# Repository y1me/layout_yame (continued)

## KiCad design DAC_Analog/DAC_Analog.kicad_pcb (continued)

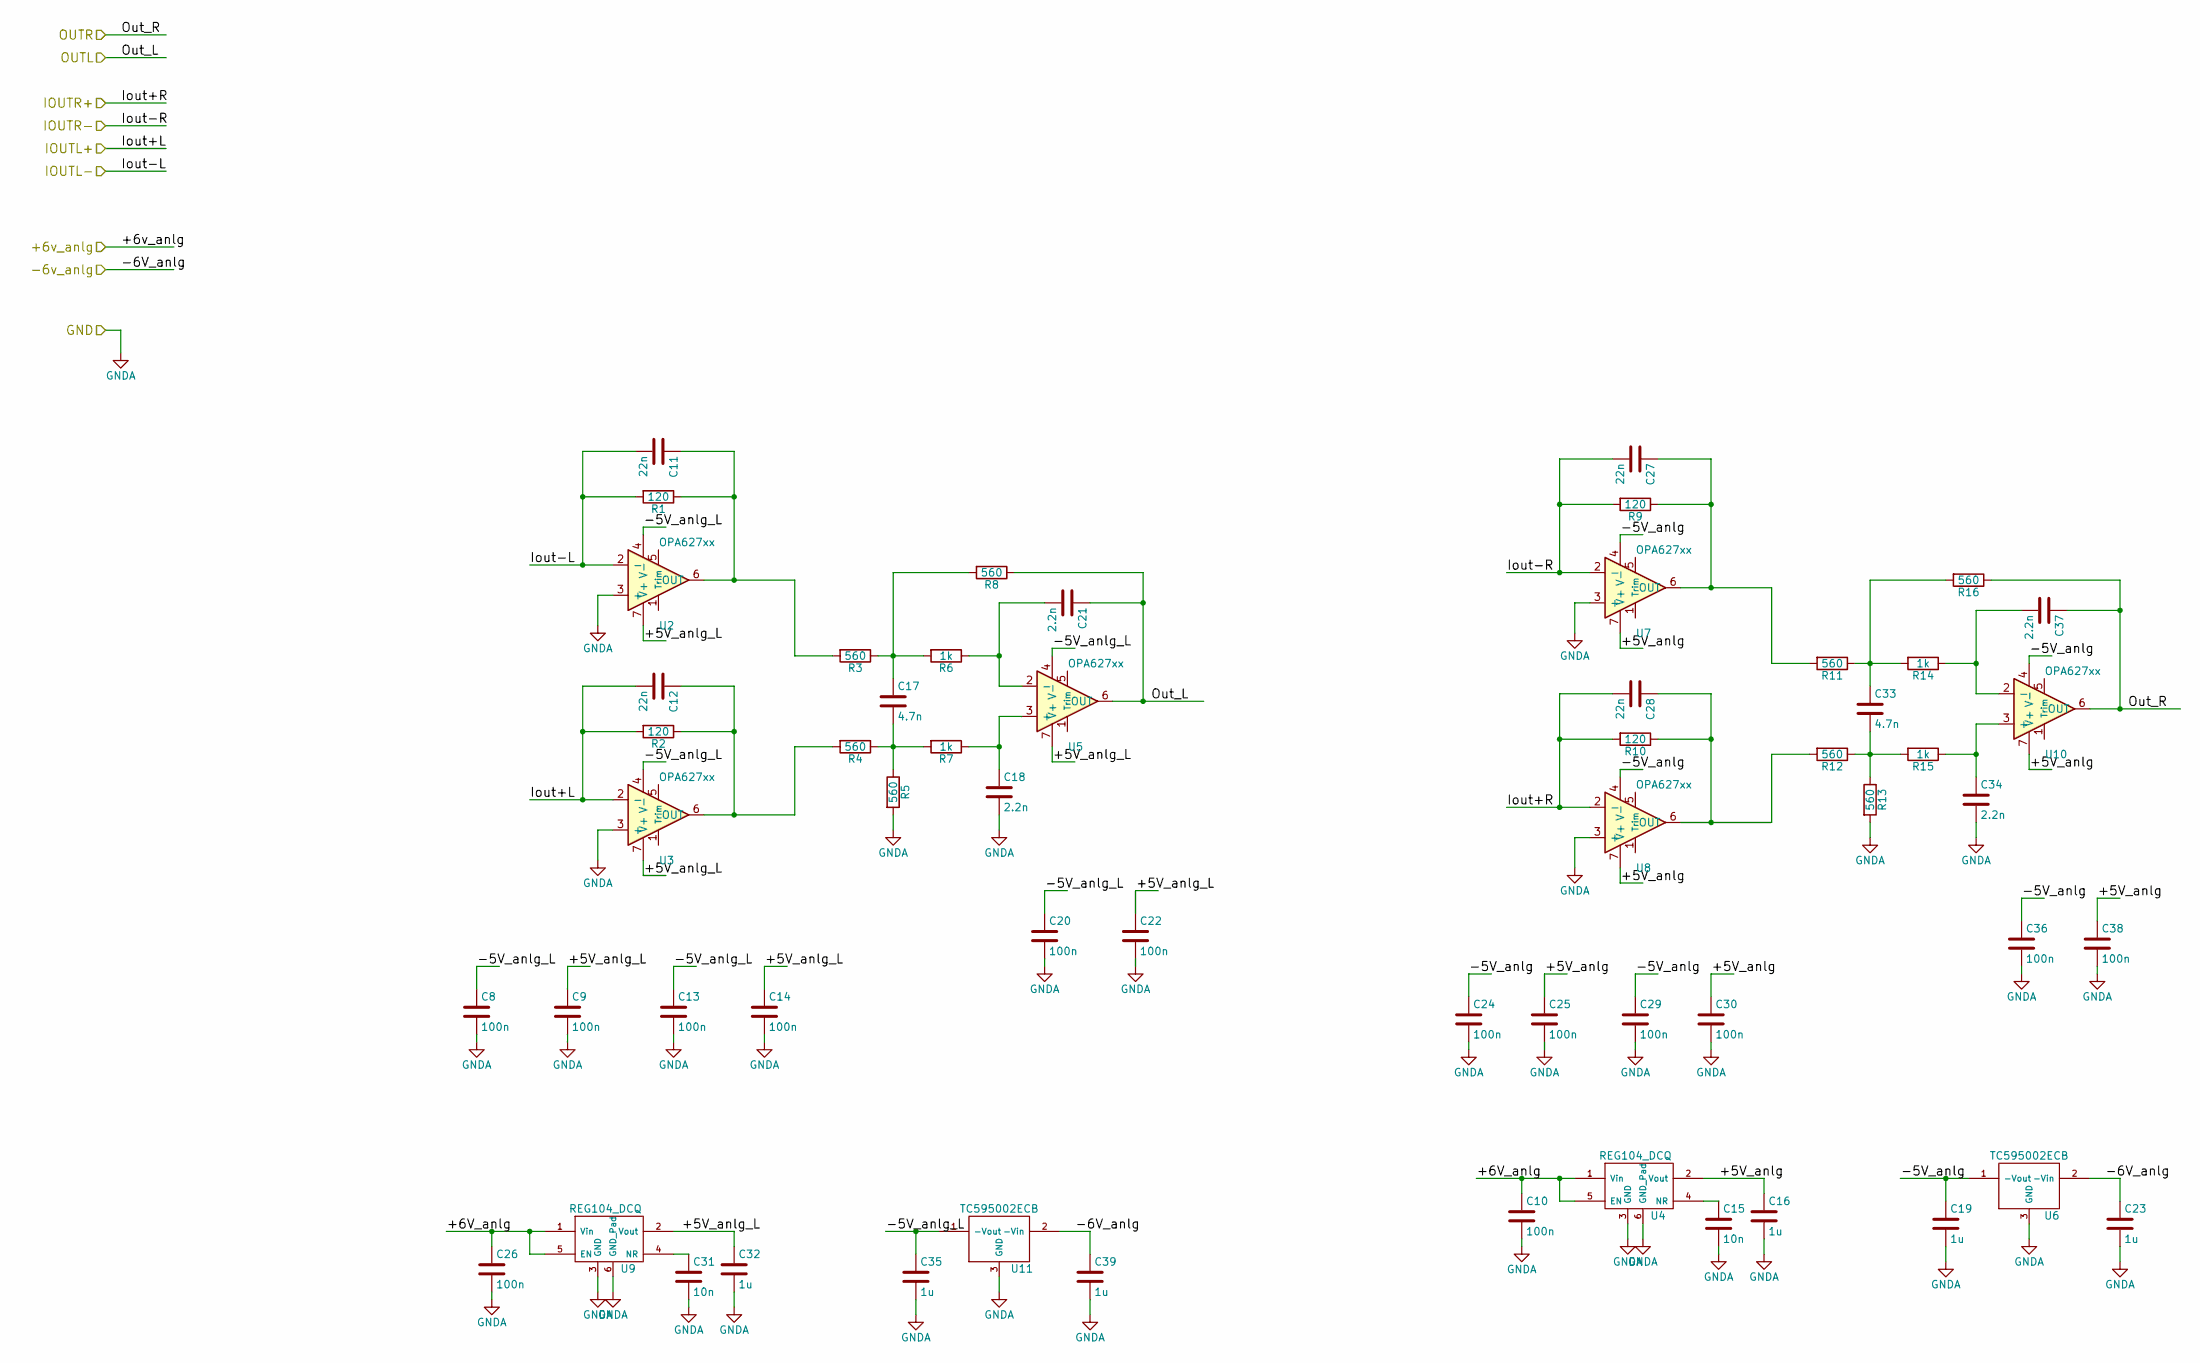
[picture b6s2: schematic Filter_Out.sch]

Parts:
C8, C9, C10, C13, C14, C20, C22, C24, C25, C26, C29, C30, C36, C38: 100n; SM0603-MR
C11, C12, C27, C28: 22n; C_Rect_L10.3mm_W5.0mm_P7.50mm_MKS4
C15, C31: 10n; SM0603-MR
C16, C19, C23, C32, C35, C39: 1u; SM0805-MR
C17, C33: 4.7n; C_Disc_D11.0mm_W5.0mm_P5.00mm
C18, C21, C34, C37: 2.2n; C_Disc_D11.0mm_W5.0mm_P5.00mm
R1, R2, R9, R10: 120; SM0603-MR
R3, R4, R5, R8, R11, R12, R13, R16: 560; SM0603-MR
R6, R7, R14, R15: 1k; SM0603-MR
U2, U3, U5, U7, U8, U10: OPA627xx; DIP-8_W7.62mm_Socket_LongPads
U4, U9: REG104_DCQ; SOT-223-6
U6, U11: TC595002ECB; SOT23-MR

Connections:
/+6v_anlg: C10.1, C26.1, U4.1 (Vin), U4.5 (EN), U9.1 (Vin), U9.5 (EN); also elsewhere on the board
/-6V_anlg: C23.1, C39.1, U6.2 (-Vin), U11.2 (-Vin); also elsewhere on the board
/Filter_Out/+5V_anlg: C16.1, C25.1, C30.1, C38.1, U4.2 (Vout), U7.7 (V+), U8.7 (V+), U10.7 (V+)
/Filter_Out/+5V_anlg_L: C9.1, C14.1, C22.1, C32.1, U2.7 (V+), U3.7 (V+), U5.7 (V+), U9.2 (Vout)
/Filter_Out/-5V_anlg: C19.1, C24.1, C29.1, C36.1, U6.1 (-Vout), U7.4 (V-), U8.4 (V-), U10.4 (V-)
/Filter_Out/-5V_anlg_L: C8.1, C13.1, C20.1, C35.1, U2.4 (V-), U3.4 (V-), U5.4 (V-), U11.1 (-Vout)
/IOUTL_N: C11.2, R1.2, U2.2 (-); also elsewhere on the board
/IOUTL_P: C12.2, R2.2, U3.2 (-); also elsewhere on the board
/IOUTR_N: C27.2, R9.2, U7.2 (-); also elsewhere on the board
/IOUTR_P: C28.2, R10.2, U8.2 (-); also elsewhere on the board
/Out_L: C21.1, R8.1, U5.6 (OUT); also elsewhere on the board
/Out_R: C37.1, R16.1, U10.6 (OUT); also elsewhere on the board
GND: C8.2, C9.2, C10.2, C13.2, C14.2, C15.2, C16.2, C18.2, C19.2, C20.2, C22.2, C23.2, C24.2, C25.2, C26.2, C29.2, C30.2, C31.2, C32.2, C34.2, C35.2, C36.2, C38.2, C39.2, R5.2, R13.2, U2.3 (+), U3.3 (+), U4.3 (GND), U4.6 (GND_Pad), U6.3 (GND), U7.3 (+), U8.3 (+), U9.3 (GND), U9.6 (GND_Pad), U11.3 (GND); also elsewhere on the board
unnamed: C11.1, R1.1, R3.2, U2.6 (OUT)
unnamed: C12.1, R2.1, R4.2, U3.6 (OUT)
unnamed: C15.1, U4.4 (NR)
unnamed: C17.1, R3.1, R6.2, R8.2
unnamed: C17.2, R4.1, R5.1, R7.2
unnamed: C18.1, R7.1, U5.3 (+)
unnamed: C21.2, R6.1, U5.2 (-)
unnamed: C27.1, R9.1, R11.2, U7.6 (OUT)
unnamed: C28.1, R10.1, R12.2, U8.6 (OUT)
unnamed: C31.1, U9.4 (NR)
unnamed: C33.1, R11.1, R14.2, R16.2
unnamed: C33.2, R12.1, R13.1, R15.2
unnamed: C34.1, R15.1, U10.3 (+)
unnamed: C37.2, R14.1, U10.2 (-)

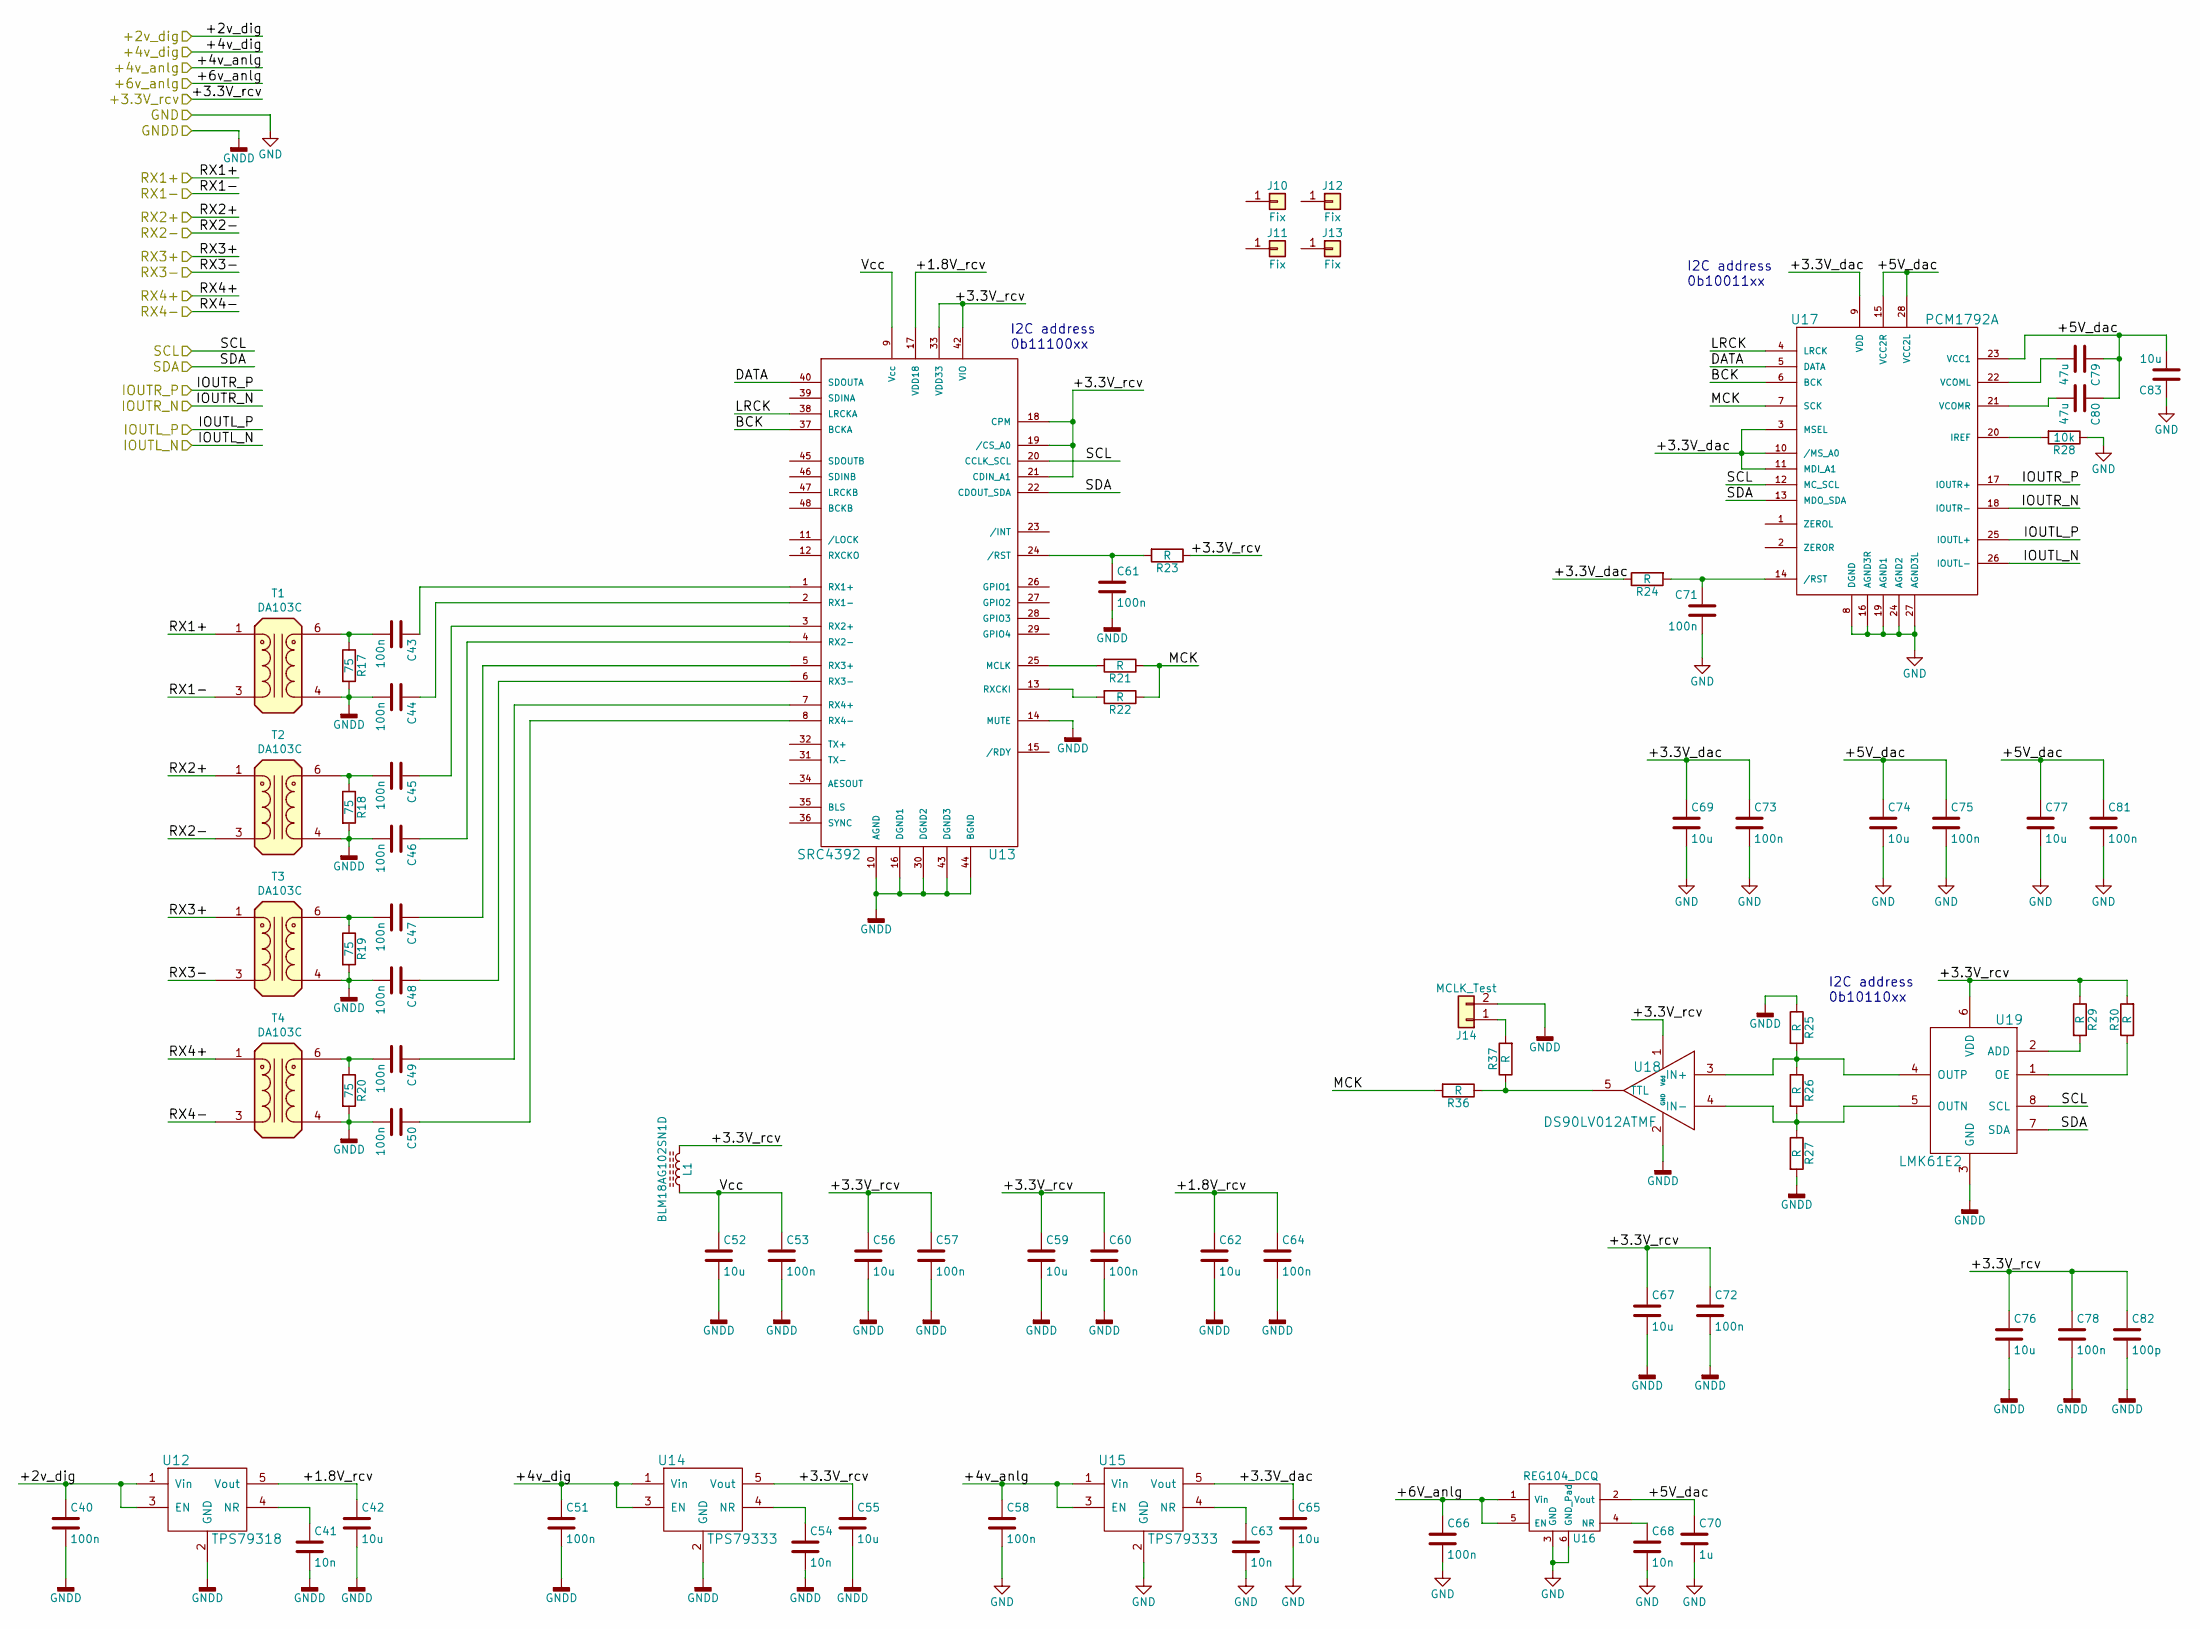
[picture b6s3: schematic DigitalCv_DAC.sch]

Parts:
C40, C43, C44, C45, C46, C47, C48, C49, C50, C51, C53, C57, C58, C60, C61, C64, C66, C71, C72, C73, C75, C78, C81: 100n; SM0603-MR
C41, C54, C63, C68: 10n; SM0603-MR
C42, C52, C55, C56, C59, C62, C65, C67, C69, C74, C76, C77, C83: 10u; SM0805-MR
C70: 1u; SM0805-MR
C79, C80: 47u; SM1206-MR
C82: 100p; SM0603-MR
J10, J11, J12, J13: Fix; MountingHole_3.2mm_M3
J14: MCLK_Test; Pin_Header_Straight_1x02_Pitch2.54mm
L1: BLM18AG102SN1D; SM0603-MR
R17, R18, R19, R20: 75; SM0603-MR
R21, R22, R23, R24, R25, R26, R27, R29, R30, R36, R37: R; SM0603-MR
R28: 10k; SM0603-MR
T1, T2, T3, T4: DA103C; DIP-6_W10.16mm_LongPads
U12: TPS79318; SOT-23-5_HandSoldering
U13: SRC4392; TQFP-48_7x7mm_Pitch0.5mm
U14, U15: TPS79333; SOT-23-5_HandSoldering
U16: REG104_DCQ; SOT-223-6
U17: PCM1792A; SSOP-28_5.3x10.2mm_Pitch0.65mm
U18: DS90LV012ATMF; SOT-23-5_HandSoldering
U19: LMK61E2; QFM_8

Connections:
/+2v_dig: C40.1, U12.1 (Vin), U12.3 (EN); also elsewhere on the board
/+3.3V_rcv: C55.1, C56.1, C57.1, C59.1, C60.1, C67.1, C72.1, C76.1, C78.1, C82.1, L1.1, R23.1, R29.1, R30.2, U13.18 (CPM), U13.19 (/CS_A0), U13.21 (CDIN_A1), U13.33 (VDD33), U13.42 (VIO), U14.5 (Vout), U18.1 (Vdd), U19.6 (VDD); also elsewhere on the board
/+4v_anlg: C58.1, U15.1 (Vin), U15.3 (EN); also elsewhere on the board
/+4v_dig: C51.1, U14.1 (Vin), U14.3 (EN); also elsewhere on the board
/+6v_anlg: C66.1, U16.1 (Vin), U16.5 (EN); also elsewhere on the board
/DigitalCv_DAC/+1.8V_rcv: C42.1, C62.1, C64.1, U12.5 (Vout), U13.17 (VDD18)
/DigitalCv_DAC/+3.3V_dac: C65.1, C69.1, C73.1, R24.1, U15.5 (Vout), U17.3 (MSEL), U17.9 (VDD), U17.10 (/MS_A0), U17.11 (MDI_A1)
/DigitalCv_DAC/+5V_dac: C70.1, C74.1, C75.1, C77.1, C79.1, C80.1, C81.1, C83.2, U16.2 (Vout), U17.15 (VCC2R), U17.23 (VCC1), U17.28 (VCC2L)
/DigitalCv_DAC/BCK: U13.37 (BCKA), U17.6 (BCK)
/DigitalCv_DAC/DATA: U13.40 (SDOUTA), U17.5 (DATA)
/DigitalCv_DAC/LRCK: U13.38 (LRCKA), U17.4 (LRCK)
/DigitalCv_DAC/MCK: R21.1, R22.1, R36.2, U17.7 (SCK)
/DigitalCv_DAC/Vcc: C52.1, C53.1, L1.2, U13.9 (Vcc)
/IOUTL_N: U17.26 (IOUTL-); also elsewhere on the board
/IOUTL_P: U17.25 (IOUTL+); also elsewhere on the board
/IOUTR_N: U17.18 (IOUTR-); also elsewhere on the board
/IOUTR_P: U17.17 (IOUTR+); also elsewhere on the board
/RX1+: T1.1 (AA); also elsewhere on the board
/RX1-: T1.3 (AB); also elsewhere on the board
/RX2+: T2.1 (AA); also elsewhere on the board
/RX2-: T2.3 (AB); also elsewhere on the board
/RX3+: T3.1 (AA); also elsewhere on the board
/RX3-: T3.3 (AB); also elsewhere on the board
/RX4+: T4.1 (AA); also elsewhere on the board
/RX4-: T4.3 (AB); also elsewhere on the board
/SCL: U13.20 (CCLK_SCL), U17.12 (MC_SCL), U19.8 (SCL); also elsewhere on the board
/SDA: U13.22 (CDOUT_SDA), U17.13 (MDO_SDA), U19.7 (SDA); also elsewhere on the board
GND: C40.2, C41.2, C42.2, C44.2, C46.2, C48.2, C50.2, C51.2, C52.2, C53.2, C54.2, C55.2, C56.2, C57.2, C58.2, C59.2, C60.2, C61.2, C62.2, C63.2, C64.2, C65.2, C66.2, C67.2, C68.2, C69.2, C70.2, C71.2, C72.2, C73.2, C74.2, C75.2, C76.2, C77.2, C78.2, C81.2, C82.2, C83.1, J14.2, R17.2, R18.2, R19.2, R20.2, R25.1, R27.2, R28.1, T1.4 (SA), T2.4 (SA), T3.4 (SA), T4.4 (SA), U12.2 (GND), U13.10 (AGND), U13.14 (MUTE), U13.16 (DGND1), U13.30 (DGND2), U13.43 (DGND3), U13.44 (BGND), U14.2 (GND), U15.2 (GND), U16.3 (GND), U16.6 (GND_Pad), U17.8 (DGND), U17.16 (AGND3R), U17.19 (AGND1), U17.24 (AGND2), U17.27 (AGND3L), U18.2 (GND), U19.3 (GND); also elsewhere on the board
unnamed: C41.1, U12.4 (NR)
unnamed: C43.1, U13.1 (RX1+)
unnamed: C43.2, R17.1, T1.6 (SB)
unnamed: C44.1, U13.2 (RX1-)
unnamed: C45.1, U13.3 (RX2+)
unnamed: C45.2, R18.1, T2.6 (SB)
unnamed: C46.1, U13.4 (RX2-)
unnamed: C47.1, U13.5 (RX3+)
unnamed: C47.2, R19.1, T3.6 (SB)
unnamed: C48.1, U13.6 (RX3-)
unnamed: C49.1, U13.7 (RX4+)
unnamed: C49.2, R20.1, T4.6 (SB)
unnamed: C50.1, U13.8 (RX4-)
unnamed: C54.1, U14.4 (NR)
unnamed: C61.1, R23.2, U13.24 (/RST)
unnamed: C63.1, U15.4 (NR)
unnamed: C68.1, U16.4 (NR)
unnamed: C71.1, R24.2, U17.14 (/RST)
unnamed: C79.2, U17.22 (VCOML)
unnamed: C80.2, U17.21 (VCOMR)
unnamed: J14.1, R37.2
unnamed: R21.2, U13.25 (MCLK)
unnamed: R22.2, U13.13 (RXCKI)
unnamed: R25.2, R26.1, U18.3 (IN+), U19.4 (OUTP)
unnamed: R26.2, R27.1, U18.4 (IN-), U19.5 (OUTN)
unnamed: R28.2, U17.20 (IREF)
unnamed: R29.2, U19.2 (ADD)
unnamed: R30.1, U19.1 (OE)
unnamed: R36.1, R37.1, U18.5 (TTL)

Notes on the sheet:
I2C address 0b11100xx
I2C address 0b10011xx
I2C address 0b10110xx

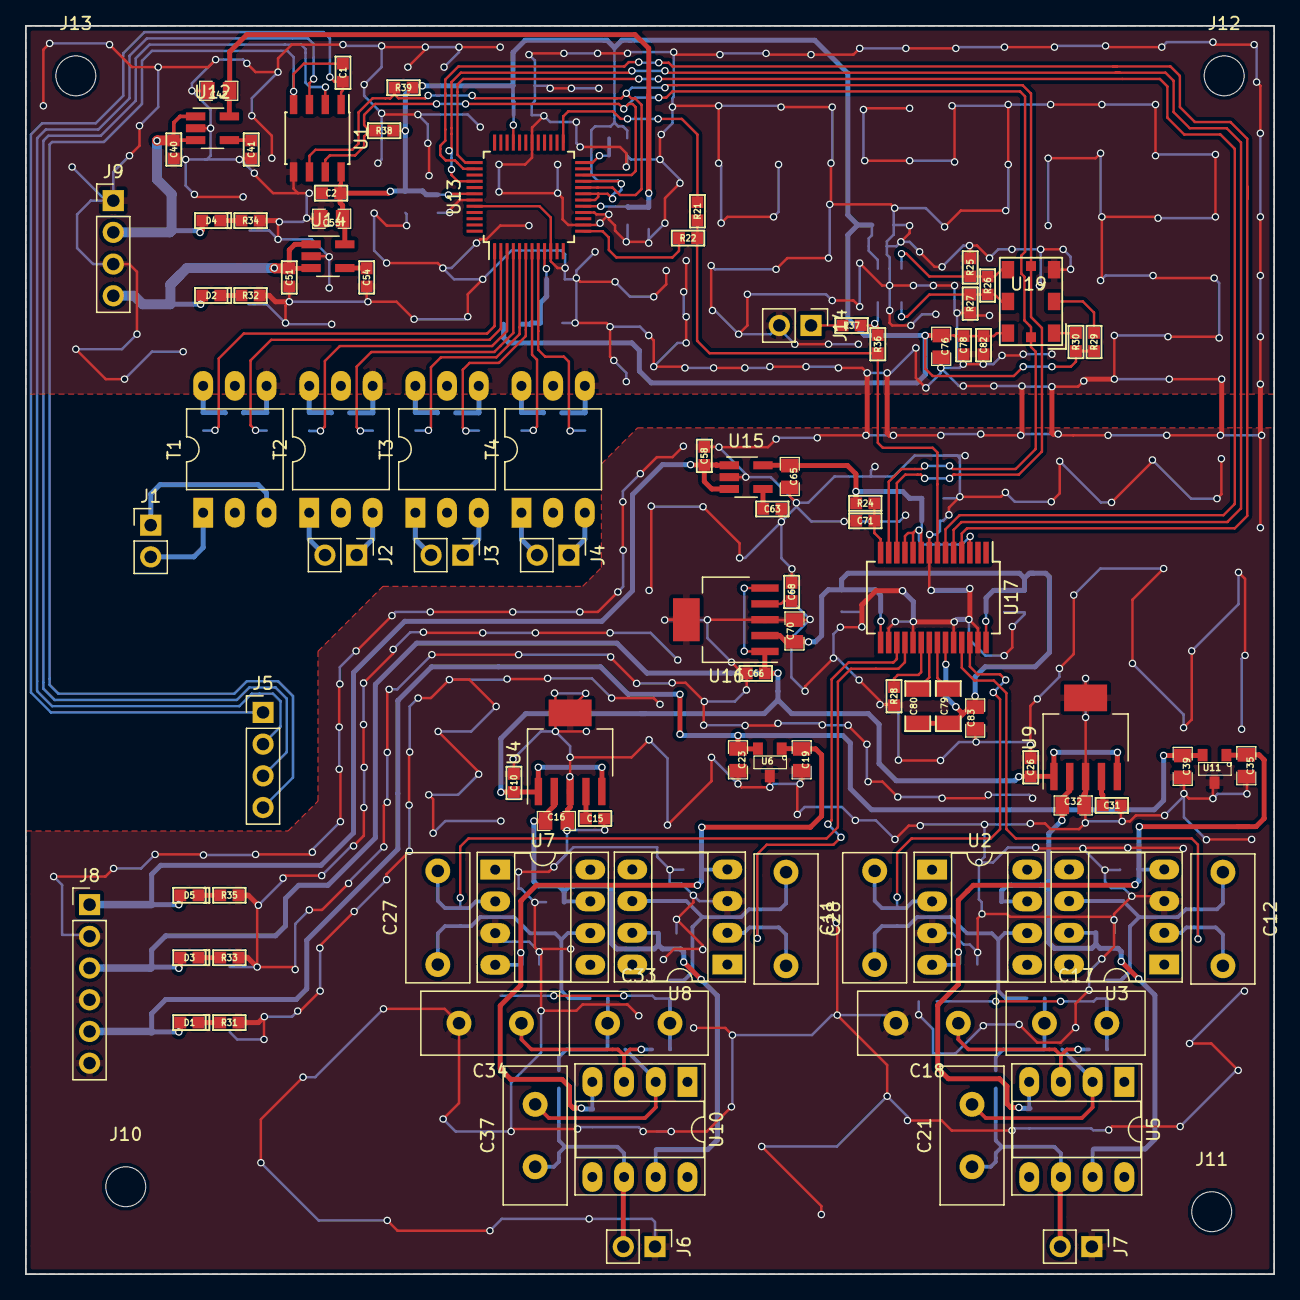
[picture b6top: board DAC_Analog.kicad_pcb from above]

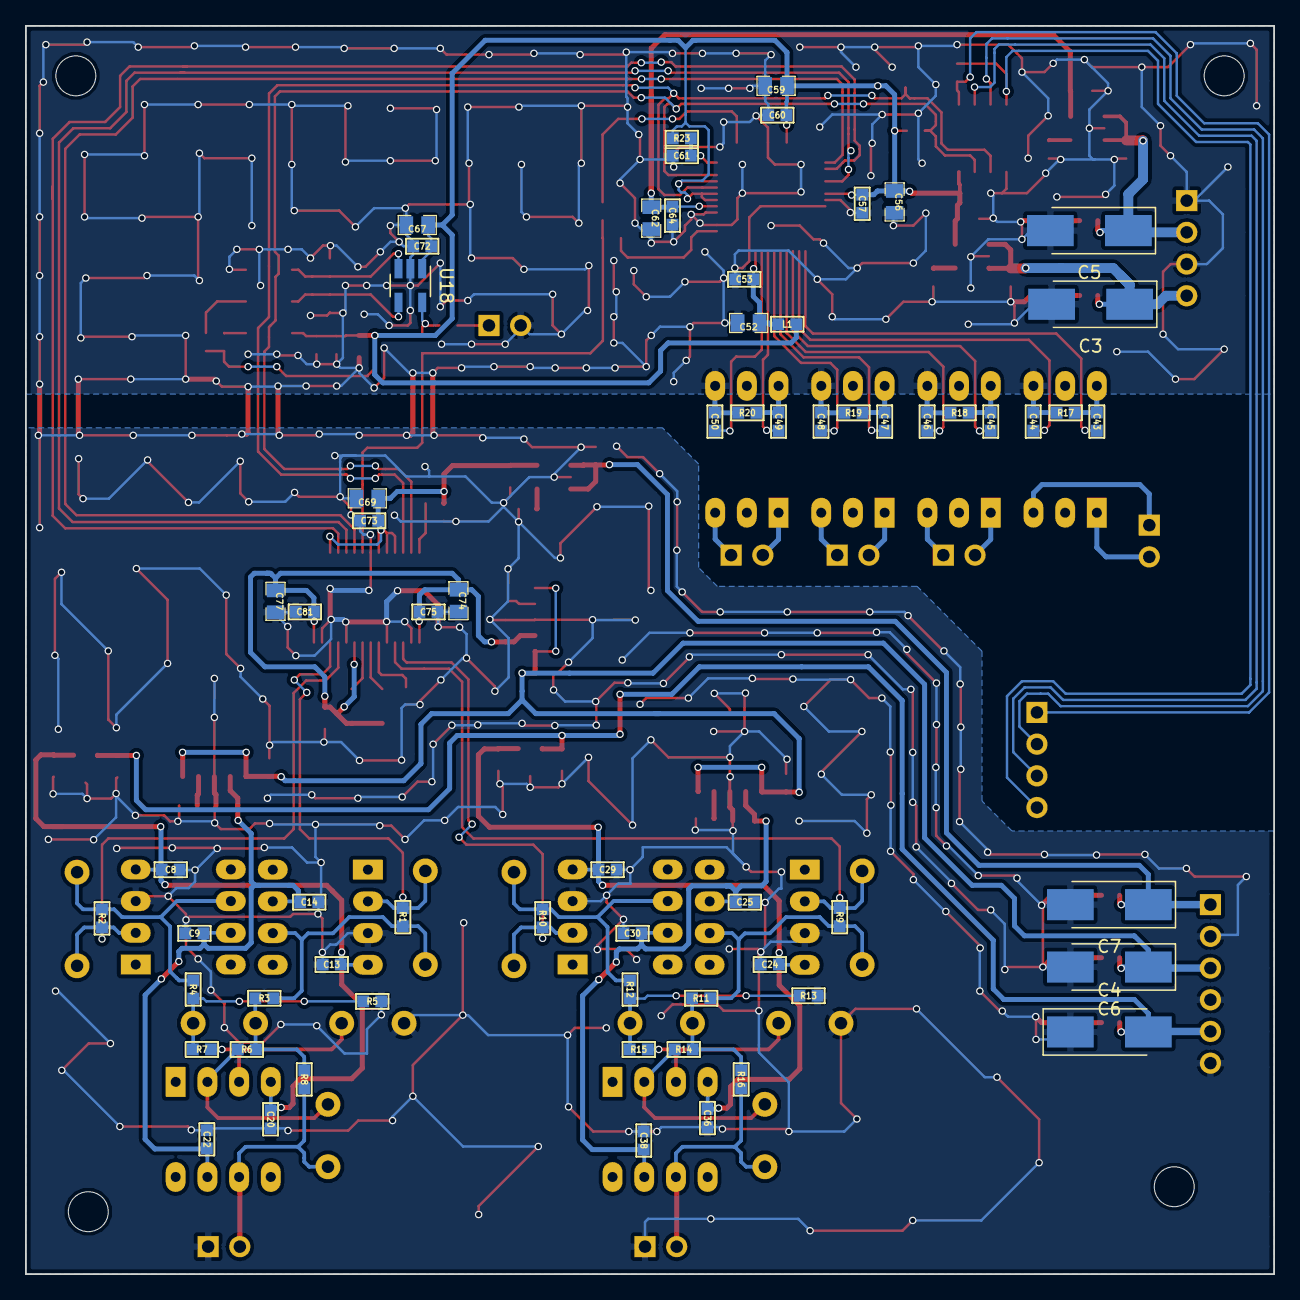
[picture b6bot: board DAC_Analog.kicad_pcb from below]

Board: 2 copper layers, 100.0 x 100.0 mm, 165 parts (65 on the bottom side), 87 nets.

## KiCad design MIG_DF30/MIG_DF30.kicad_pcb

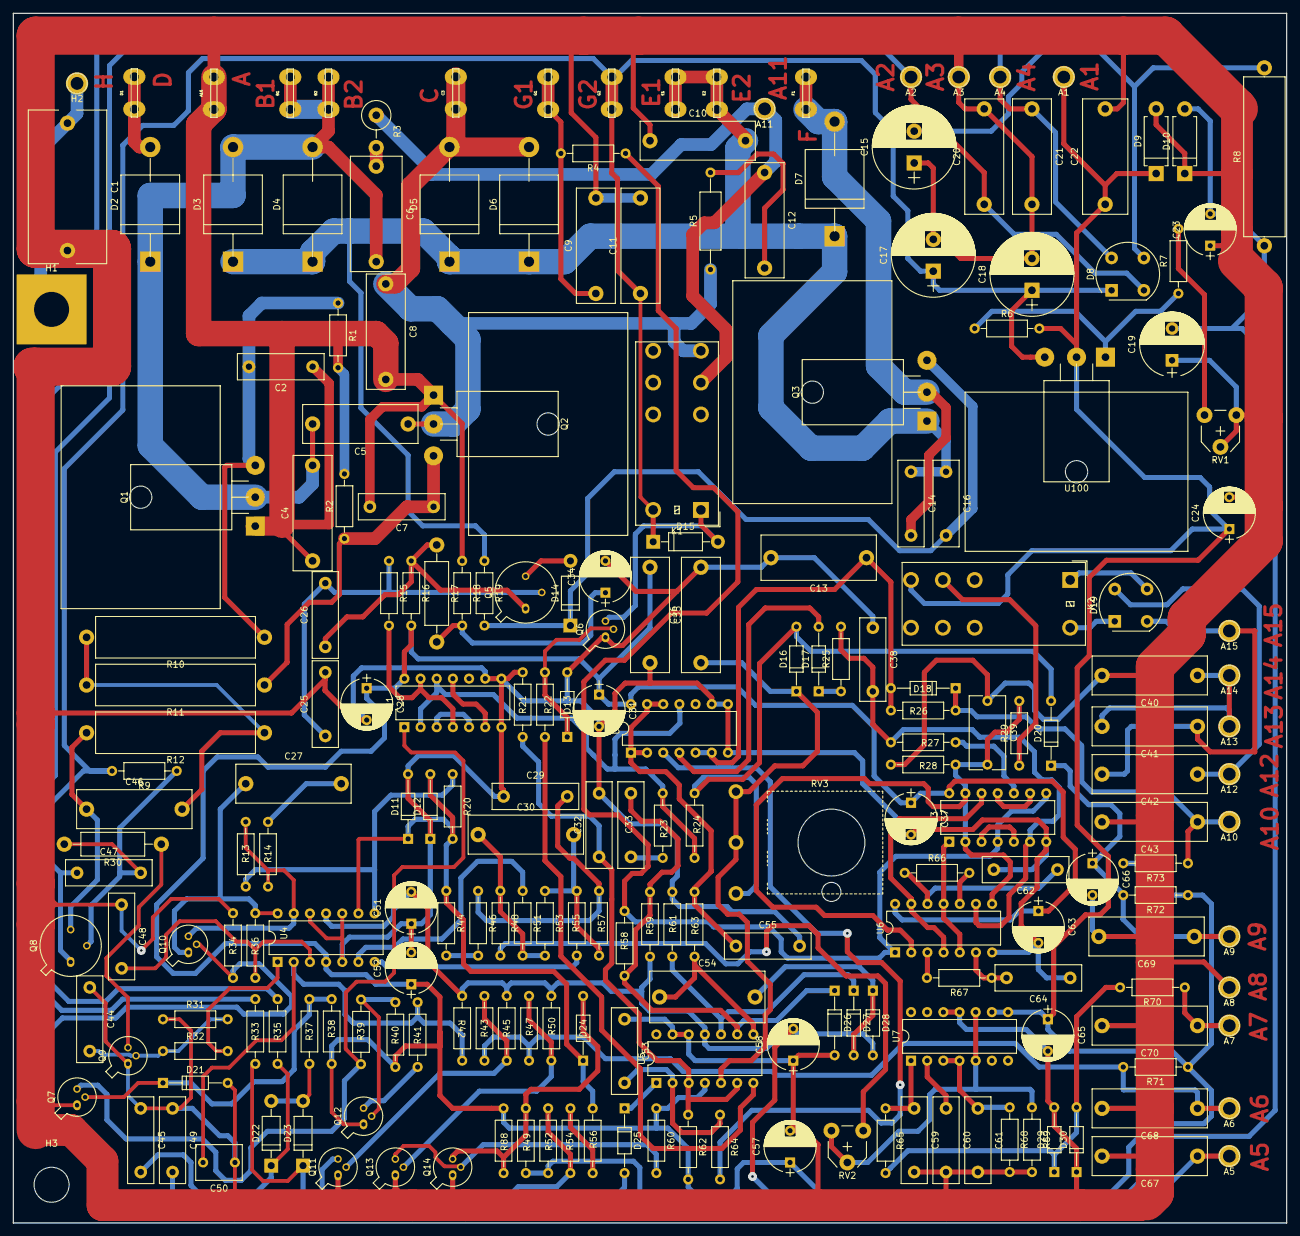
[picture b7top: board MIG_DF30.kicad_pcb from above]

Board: 2 copper layers, 200.0 x 190.0 mm, 225 parts (0 on the bottom side), 110 nets.

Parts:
A1, A2, A3, A4, A5, A6, A7, A8, A9, A10, A11, A12, A13, A14, A15: Conn_01x01_Male; Pin_d2mm_L11.0mm
A16: Conn_01x01_Male; FASTON Printed Circuit Board Tabs
B1, B2: Conn_01x01_Male; FASTON Printed Circuit Board Tabs
C1: 0,1u; C_Rect_L24.0mm_W12.2mm_P20mm_MKT
C2, C7, C14, C16, C25, C29, C32, C33, C44, C45, C47, C48, C49, C55, C59, C61: 100n; C_Rect_L13.5mm_W4.0mm_P10.00mm_FKS3_FKP3_MKS4
C3: Conn_01x01_Male; FASTON Printed Circuit Board Tabs
C4: C; C_Rect_L18.0mm_W6.0mm_P15.00mm_FKS3_FKP3
C5, C46: 1u; C_Rect_L18.0mm_W6.0mm_P15.00mm_FKS3_FKP3
C6: 1u; C_Rect_L18.0mm_W8.0mm_P15.00mm_FKS3_FKP3
C8, C9, C10, C11, C20, C21, C35, C40, C41, C42, C43, C67, C68, C69, C70: 0,1u; C_Rect_L18.0mm_W6.0mm_P15.00mm_FKS3_FKP3
C12: 0.1u; C_Rect_L18.0mm_W6.0mm_P15.00mm_FKS3_FKP3
C13: 2.2u; C_Rect_L18.0mm_W7.0mm_P15.00mm_FKS3_FKP3
C15, C17, C18: CP; CP_Radial_D13.0mm_P5.00mm
C19: 47u; CP_Radial_D10.0mm_P5.00mm
C22: 1u; C_Rect_L18.0mm_W7.0mm_P15.00mm_FKS3_FKP3
C23, C24, C28, C31, C34, C37, C51, C52, C57, C58, C63, C65, C66: 10u; CP_Radial_D8.0mm_P5.00mm
C26, C53, C60: 10n; C_Rect_L13.5mm_W4.0mm_P10.00mm_FKS3_FKP3_MKS4
C27, C30: 680n; C_Rect_L18.0mm_W6.0mm_P15.00mm_FKS3_FKP3
C36: 1.5u; C_Rect_L18.0mm_W6.0mm_P15.00mm_FKS3_FKP3
C38: C; C_Rect_L13.0mm_W4.0mm_P10.00mm_FKS3_FKP3_MKS4
C39: 470n; C_Rect_L11.5mm_W5.6mm_P10.00mm_MKT
C50: 100n; C_Rect_L7.2mm_W5.5mm_P5.00mm_FKS2_FKP2_MKS2_MKP2
C54: 2.2u; C_Rect_L18.0mm_W8.0mm_P15.00mm_FKS3_FKP3
C62, C64: 330n; C_Rect_L13.5mm_W4.0mm_P10.00mm_FKS3_FKP3_MKS4
D1: Conn_01x01_Male; FASTON Printed Circuit Board Tabs
D2, D3, D4, D5, D6, D7: MR754; D_P600_R-6_P18.00mm_Horizontal
D8, D19: SKB1,2/04; Diode_Bridge_Round_D9.8mm
D9, D10: D; D_DO-15_P10.16mm_Horizontal
D11, D12, D13, D16, D17, D18, D20, D21, D24, D25, D26, D27, D28, D29, D30: 1N4148; D_DO-35_SOD27_P10.16mm_Horizontal
D14, D15, D22, D23: D; D_DO-41_SOD81_P10.16mm_Horizontal
E1, E2: Conn_01x01_Male; FASTON Printed Circuit Board Tabs
F1: Conn_01x01_Male; FASTON Printed Circuit Board Tabs
G1, G2: Conn_01x01_Male; FASTON Printed Circuit Board Tabs
H1: MountingHole_Pad; MountingHole_5.5mm_Square_Pad
H2: Conn_01x01_Male; Pin_d2mm_L11.0mm
H3: MountingHole_Pad; MountingHole_5.5mm
K1, K2: G5V-2; Relay_DPDT_1
Q1, Q2, Q3: 2N6507; TO-220-3_Horizontal_1
Q5: 2N5415; TO-39-3
Q6, Q7, Q9, Q11, Q13, Q14: BC107A; TO-18-3
Q8: BC161-16; TO-39-3
Q10: Q_NJFET_SGD; TO-18-3
Q12: BC177A; TO-18-3
R1, R2, R19: 100; R_Axial_DIN0207_L6.3mm_D2.5mm_P10.16mm_Horizontal
R3: 220; R_Axial_DIN0414_L11.9mm_D4.5mm_P5.08mm_Vertical
R4, R21, R23, R24, R36, R37, R40, R46, R51, R60, R62, R65, R69, R70, R71: 10k; R_Axial_DIN0207_L6.3mm_D2.5mm_P10.16mm_Horizontal
R5: 1k-1/2W; R_Axial_DIN0309_L9.0mm_D3.2mm_P15.24mm_Horizontal
R6: 220; R_Axial_DIN0207_L6.3mm_D2.5mm_P10.16mm_Horizontal
R7, R16: 2k2; R_Axial_DIN0207_L6.3mm_D2.5mm_P10.16mm_Horizontal
R8: 330 ohm 5W; R_Axial_Power_L25.0mm_W6.4mm_P27.94mm
R9, R15, R25, R33, R35, R41: 1k; R_Axial_DIN0207_L6.3mm_D2.5mm_P10.16mm_Horizontal
R10, R11: 220 ohm 5W; R_Axial_Power_L25.0mm_W6.4mm_P27.94mm
R12: 270 ohm 5W; R_Axial_Power_L25.0mm_W6.4mm_P27.94mm
R13: 680k; R_Axial_DIN0207_L6.3mm_D2.5mm_P10.16mm_Horizontal
R14, R20: 330k; R_Axial_DIN0207_L6.3mm_D2.5mm_P10.16mm_Horizontal
R17: 180-1/2W; R_Axial_DIN0411_L9.9mm_D3.6mm_P15.24mm_Horizontal
R18, R22, R31, R56, R58: 18k; R_Axial_DIN0207_L6.3mm_D2.5mm_P10.16mm_Horizontal
R26, R28, R34, R64, R68, R73: 100k; R_Axial_DIN0207_L6.3mm_D2.5mm_P10.16mm_Horizontal
R27, R38: 22k; R_Axial_DIN0207_L6.3mm_D2.5mm_P10.16mm_Horizontal
R29, R43, R47, R48, R63: 47k; R_Axial_DIN0207_L6.3mm_D2.5mm_P10.16mm_Horizontal
R30: 2k2-1/2W; R_Axial_DIN0411_L9.9mm_D3.6mm_P15.24mm_Horizontal
R32, R59: 39k; R_Axial_DIN0207_L6.3mm_D2.5mm_P10.16mm_Horizontal
R39: 15k; R_Axial_DIN0207_L6.3mm_D2.5mm_P10.16mm_Horizontal
R42, R45, R50: 150k; R_Axial_DIN0207_L6.3mm_D2.5mm_P10.16mm_Horizontal
R44: 1k25; R_Axial_DIN0207_L6.3mm_D2.5mm_P10.16mm_Horizontal
R49, R72: 220k; R_Axial_DIN0207_L6.3mm_D2.5mm_P10.16mm_Horizontal
R52: 56k; R_Axial_DIN0207_L6.3mm_D2.5mm_P10.16mm_Horizontal
R53: 15K; R_Axial_DIN0207_L6.3mm_D2.5mm_P10.16mm_Horizontal
R54: 22K; R_Axial_DIN0207_L6.3mm_D2.5mm_P10.16mm_Horizontal
R55: 4k7; R_Axial_DIN0207_L6.3mm_D2.5mm_P10.16mm_Horizontal
R57: 337; R_Axial_DIN0207_L6.3mm_D2.5mm_P10.16mm_Horizontal
R61: 182k; R_Axial_DIN0207_L6.3mm_D2.5mm_P10.16mm_Horizontal
R66, R67: 390k; R_Axial_DIN0207_L6.3mm_D2.5mm_P10.16mm_Horizontal
R88: NC; R_Axial_DIN0207_L6.3mm_D2.5mm_P10.16mm_Horizontal
RV1: 500; Potentiometer_Trimmer_VishaySpectrol_Econtrim-Type36T
RV2: 50k; Potentiometer_Trimmer_VishaySpectrol_Econtrim-Type36T
RV3: R_POT; Potentiometer_MIG
U1, U2, U6: 4001; DIP-14_W7.62mm
U3: 4011; DIP-14_W7.62mm
U4, U5: LM324; DIP-14_W7.62mm
U7: LM2907N; DIP-14_W7.62mm
U100: LM317_3PinPackage; TO-220-3_Horizontal_1

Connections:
/+15V: A1.1, C22.1, C24.1, C28.1, C31.1, C35.1, C37.1, C52.1, C57.1, C63.1, C65.1, D9.1, K2.9, Q12.1, R6.2, R16.2, R38.2, R40.1, R60.1, R62.2, R71.1, R72.1, R73.2, R88.1, U1.14, U2.14, U3.14, U4.4, U5.4, U6.14, U7.8, U7.9, U100.2
/-15V: C19.2, C23.2, C51.2, C58.2, D10.2, D28.2, R8.1, R42.1, R45.1, R50.1, R59.2, U4.11, U5.11
/A2: A2.1, C20.1, D8.2, R35.1
/A4: A4.1, C21.1, D8.4, R33.1
/G2: C11.1, C17.1, C18.1, C47.1, D8.1, D15.1, G2.1, K1.1, Q8.1, R9.2, U100.3
/Q2_G: C7.1, Q2.3, R2.1, R11.1
/Q3_G: C16.2, D14.1, Q3.3, R19.2
GND: A3.1, A8.1, A16.1, C1.2, C2.1, C4.1, C7.2, C8.2, C9.2, C10.1, C11.2, C13.2, C15.1, C17.2, C18.2, C19.1, C20.2, C21.2, C22.2, C23.1, C24.2, C25.2, C28.2, C29.1, C31.2, C32.2, C34.2, C35.2, C36.2, C37.2, C38.1, C39.1, C40.2, C43.2, C44.1, C45.1, C48.1, C49.1, C50.1, C51.1, C52.2, C53.1, C55.2, C57.2, C58.1, C59.2, C60.2, C61.2, C62.2, C63.2, C64.1, C65.2, C66.2, C67.2, C68.2, C69.2, C70.2, D9.2, D10.1, D11.2, D12.1, D13.2, D21.2, D26.2, D29.2, D30.1, Q1.1, Q2.1, Q6.1, Q7.1, Q9.1, Q11.1, Q13.1, Q14.1, R1.2, R2.2, R18.1, R21.1, R28.2, R31.1, R34.1, R61.1, R68.2, R69.2, RV1.1, RV1.2, U1.7, U1.8, U1.9, U2.7, U2.8, U2.9, U3.7, U4.5, U4.10, U4.12, U5.12, U5.13, U6.7, U7.11, U7.12
unnamed: A5.1, C67.1, R49.2, R52.2
unnamed: A6.1, C68.1, R43.2, R47.2, R71.2
unnamed: A7.1, C70.1, R70.1
unnamed: A9.1, C66.1, C69.1, D20.1, R72.2
unnamed: A10.1, C43.1, D18.1, R26.1, R73.1
unnamed: A11.1, C12.1, K1.13, R3.1
unnamed: A12.1, C42.1, D19.4
unnamed: A13.1, A14.1, C40.1, C41.2
unnamed: A15.1, C41.1, C42.2, D19.2
unnamed: B1.1, B2.1, C4.2, C5.2, C6.2, D2.1, D3.2, D4.2, Q1.2
unnamed: C1.1, H1.1, H2.1
unnamed: C2.2, Q1.3, R1.1, R10.1
unnamed: C3.1, C5.1, C8.1, D5.2, D6.2, K1.9, Q2.2, R5.1
unnamed: C6.1, R3.2
unnamed: C9.1, G1.1, R4.2
unnamed: C10.2, C14.1, C16.1, D3.1, D4.1, D5.1, D6.1, D7.1, E1.1, E2.1, Q3.1, R19.1
unnamed: C12.2, R5.2
unnamed: C13.1, D18.2, R26.2, U2.5, U2.6
unnamed: C14.2, D7.2, F1.1, Q3.2
unnamed: C15.2, D8.3, R8.2
unnamed: C25.1, C26.2, Q5.2, R15.1
unnamed: C26.1, Q5.1, R16.1, R17.1
unnamed: C27.1, Q10.1, R36.1, U4.14
unnamed: C27.2, R14.1
unnamed: C29.2, R46.1, R57.1
unnamed: C30.1, R48.1, R51.2, R53.2
unnamed: C30.2, R53.1, R55.1, R57.2
unnamed: C32.1, R21.2, R62.1, U5.3, U5.6
unnamed: C33.1, R23.2
unnamed: C33.2, D26.1, R58.2, R59.1, U5.9
unnamed: C34.1, R17.2, R18.2
unnamed: C36.1, D16.1, RV3.2, RV3.3, U5.5
unnamed: C38.2, R25.2, R27.2, U3.6, U6.9
unnamed: C39.2, R28.1, R29.2, U3.2, U3.13, U6.2, U6.8
unnamed: C44.2, Q9.2, R31.2, R32.1
unnamed: C45.2, D22.1, R35.2
unnamed: C46.1, Q8.3, R12.2
unnamed: C46.2, R10.2, R11.2, R12.1
unnamed: C47.2, Q8.2, R9.1, R30.2
unnamed: C48.2, R36.2, U4.3
unnamed: C49.2, D23.1, R33.2
unnamed: C50.2, R41.1, R42.2, U4.2
unnamed: C53.2, R64.1, U5.2
unnamed: C54.1, R63.2, U5.8
unnamed: C54.2, D27.2, D28.1
unnamed: C55.1, R63.1, U2.1, U2.2, U2.12, U2.13
unnamed: C59.1, R65.1, U7.1
unnamed: C60.1, U7.2
unnamed: C61.1, R68.1, U7.3, U7.4
unnamed: C62.1, R66.1, U6.12
unnamed: C64.2, R67.1, U6.6
unnamed: D1.1, D2.2
unnamed: D11.1, D12.2, D24.1, R20.2, R44.1, R56.1, U4.9
unnamed: D13.1, Q6.2, R22.1
unnamed: D14.2, Q5.3
unnamed: D15.2, K1.16, Q6.3
unnamed: D16.2, D20.2, R24.1, RV3.1
unnamed: D17.1, R25.1
unnamed: D17.2, U2.4
unnamed: D19.1, K2.1
unnamed: D19.3, K2.16
unnamed: D21.1, Q7.2, R37.1, R38.1
unnamed: D22.2, D23.2, R37.2
unnamed: D24.2, Q14.3, R49.1, R88.2
unnamed: D25.1, U5.1
unnamed: D25.2, Q10.2, R34.2
unnamed: D27.1, R61.2, U5.10
unnamed: D29.1, D30.2, R65.2, R70.2
unnamed: K2.13, R29.1
unnamed: Q7.3, R39.2, U1.1
unnamed: Q9.3, R30.1
unnamed: Q10.3, R13.1, R14.2, U4.13
unnamed: Q11.2, R43.1, R45.2
unnamed: Q11.3, R52.1, R54.2
unnamed: Q12.2, R39.1, R40.2
unnamed: Q12.3, R41.2
unnamed: Q13.2, R47.1, R50.2
unnamed: Q13.3, Q14.2, R60.2
unnamed: R4.1, R58.1, U3.4, U3.8, U6.1
unnamed: R6.1, R7.1, U100.1
unnamed: R7.2, RV1.3
unnamed: R13.2, R20.1, U4.8
unnamed: R15.2, U1.4, U1.13
unnamed: R22.2, U5.7
unnamed: R23.1, R24.2, U1.2, U1.12, U2.11
unnamed: R27.1, U3.10
unnamed: R32.2, U4.1
unnamed: R44.2, R46.2
unnamed: R48.2, RV2.1
unnamed: R51.1, U4.6
unnamed: R54.1, R56.2
unnamed: R55.2, U4.7
unnamed: R64.2, U2.3
unnamed: R66.2, U6.10
unnamed: R67.2, U6.3
unnamed: R69.1, RV2.2, RV2.3, U7.5, U7.10
unnamed: U1.3, U1.5
unnamed: U1.6, U1.11
unnamed: U3.1, U6.5, U6.11
unnamed: U3.3, U3.5
unnamed: U3.9, U3.11
unnamed: U3.12, U6.4, U6.13
